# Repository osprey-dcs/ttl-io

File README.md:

# Osprey Quartz LVTTL I/O Daughter Board

A PMOD compatible board providing 4 input and 
4 output bits of LVTTL binary I/O.
Intended to be used with LBL [Marble](https://github.com/BerkeleyLab/Marble).

* [Current design](https://osprey-dcs.github.io/ttl-io) information.

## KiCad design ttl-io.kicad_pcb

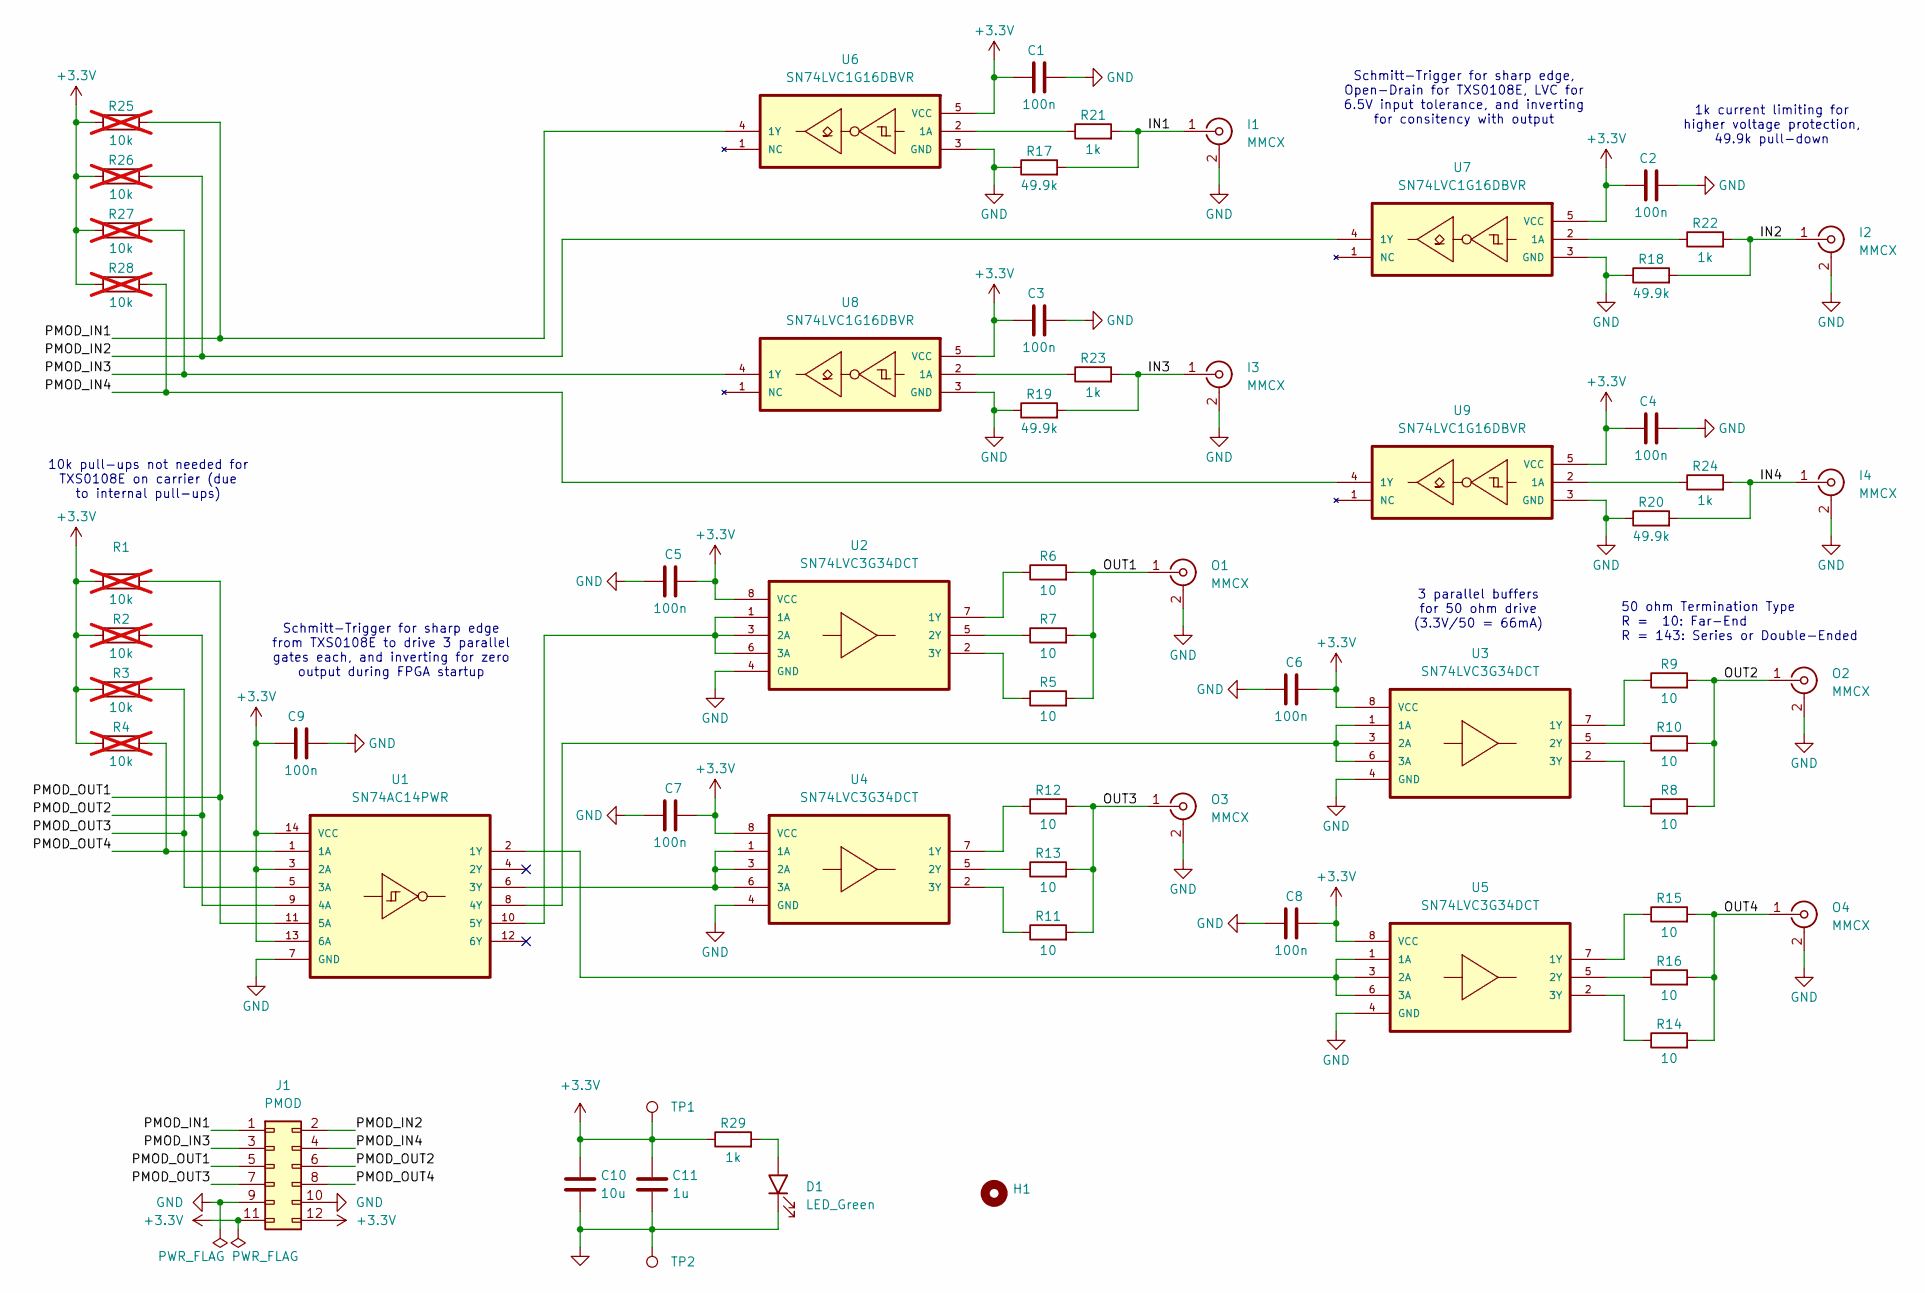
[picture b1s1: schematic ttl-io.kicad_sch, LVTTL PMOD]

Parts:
C1, C2, C3, C4, C5, C6, C7, C8, C9: 100n; C_0603_1608Metric; MPN CL10B104KB8NNWC; Digikey 1276-1935-2-ND
C10: 10u; C_0805_2012Metric; MPN GRM21BR61E106KA73L; Digikey 490-5523-2-ND
C11: 1u; C_0603_1608Metric; MPN CC0603KRX7R7BB105; Digikey 311-1446-2-ND
D1: LED_Green; LED_0603_1608Metric; MPN APT1608CGCK; Digikey 754-1116-2-ND
H1: Mounting_Hole_Slot
I1, I2, I3, I4: MMCX; MMCX_THT_Vertical; MPN MMCX-J-P-H-ST-TH1; Digikey SAM10617-ND
J1: PMOD; PMOD_2x06_P2.54mm_Mirrored; MPN PH2RA-12-UA; Digikey 2057-PH2RA-12-UA-ND
O1, O2, O3, O4: MMCX; MMCX_THT_Vertical; MPN MMCX-J-P-H-ST-TH1; Digikey SAM10617-ND
R1, R2, R3, R4, R25, R26, R27, R28: 10k; R_0603_1608Metric; MPN RC0603FR-0710KL; Digikey 311-10.0KHRCT-ND; not fitted
R5, R6, R7, R8, R9, R10, R11, R12, R13, R14, R15, R16: 10; R_0805_2012Metric; MPN RC0805FR-1010RL; Digikey 13-RC0805FR-1010RLTR-ND
R17, R18, R19, R20: 49.9k; R_0603_1608Metric; MPN RC0603FR-1349K9L; Digikey 13-RC0603FR-1349K9LTR-ND
R21, R22, R23, R24, R29: 1k; R_0603_1608Metric; MPN RC0603FR-071KP; Digikey YAG1294TR-ND
TP1: TestPointRed; TestPoint_Loop_D1.80mm_Drill1.0mm_Beaded; MPN 5000; Digikey 36-5000-ND
TP2: TestPointBlack; TestPoint_Loop_D1.80mm_Drill1.0mm_Beaded; MPN 5001; Digikey 36-5001-ND
U1: SN74AC14PWR; SN74AC1xPWR; MPN SN74AC14PWR; Digikey 296-4302-1-ND
U2, U3, U4, U5: SN74LVC3G34DCT; MPN SN74LVC3G34DCTR; Digikey 296-13285-1-ND
U6, U7, U8, U9: SN74LVC1G16DBVR; MPN SN74LVC1G16DBVR; Digikey 296-SN74LVC1G16DBVRCT-ND

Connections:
+3.3V: C1.2, C2.2, C3.2, C4.2, C5.2, C6.2, C7.2, C8.2, C9.2, C10.1, C11.1, J1.11, J1.12, R1.1, R2.1, R3.1, R4.1, R25.1, R26.1, R27.1, R28.1, R29.1, TP1.1, U1.3 (2A), U1.13 (6A), U1.14 (VCC), U2.8 (VCC), U3.8 (VCC), U4.8 (VCC), U5.8 (VCC), U6.5 (VCC), U7.5 (VCC), U8.5 (VCC), U9.5 (VCC)
/IN1: I1.1 (In), R17.2, R21.2
/IN2: I2.1 (In), R18.2, R22.2
/IN3: I3.1 (In), R19.2, R23.2
/IN4: I4.1 (In), R20.2, R24.2
/OUT1: O1.1 (In), R5.2, R6.2, R7.2
/OUT2: O2.1 (In), R8.2, R9.2, R10.2
/OUT3: O3.1 (In), R11.2, R12.2, R13.2
/OUT4: O4.1 (In), R14.2, R15.2, R16.2
/PMOD_IN1: J1.1, R25.2, U6.4 (1Y)
/PMOD_IN2: J1.2, R26.2, U7.4 (1Y)
/PMOD_IN3: J1.3, R27.2, U8.4 (1Y)
/PMOD_IN4: J1.4, R28.2, U9.4 (1Y)
/PMOD_OUT1: J1.5, R1.2, U1.11 (5A)
/PMOD_OUT2: J1.6, R2.2, U1.9 (4A)
/PMOD_OUT3: J1.7, R3.2, U1.5 (3A)
/PMOD_OUT4: J1.8, R4.2, U1.1 (1A)
GND: C1.1, C2.1, C3.1, C4.1, C5.1, C6.1, C7.1, C8.1, C9.1, C10.2, C11.2, D1.1 (K), I1.2 (Ext), I2.2 (Ext), I3.2 (Ext), I4.2 (Ext), J1.9, J1.10, O1.2 (Ext), O2.2 (Ext), O3.2 (Ext), O4.2 (Ext), R17.1, R18.1, R19.1, R20.1, TP2.1, U1.7 (GND), U2.4 (GND), U3.4 (GND), U4.4 (GND), U5.4 (GND), U6.3 (GND), U7.3 (GND), U8.3 (GND), U9.3 (GND)
unnamed: D1.2 (A), R29.2
unnamed: U1.2 (1Y), U5.1 (1A), U5.3 (2A), U5.6 (3A)
unnamed: U1.6 (3Y), U4.1 (1A), U4.3 (2A), U4.6 (3A)
unnamed: U1.8 (4Y), U3.1 (1A), U3.3 (2A), U3.6 (3A)
unnamed: U1.10 (5Y), U2.1 (1A), U2.3 (2A), U2.6 (3A)
unnamed: R6.1, U2.7 (1Y)
unnamed: R7.1, U2.5 (2Y)
unnamed: R5.1, U2.2 (3Y)
unnamed: R9.1, U3.7 (1Y)
unnamed: R10.1, U3.5 (2Y)
unnamed: R8.1, U3.2 (3Y)
unnamed: R12.1, U4.7 (1Y)
unnamed: R13.1, U4.5 (2Y)
unnamed: R11.1, U4.2 (3Y)
unnamed: R15.1, U5.7 (1Y)
unnamed: R16.1, U5.5 (2Y)
unnamed: R14.1, U5.2 (3Y)
unnamed: R21.1, U6.2 (1A)
unnamed: R22.1, U7.2 (1A)
unnamed: R23.1, U8.2 (1A)
unnamed: R24.1, U9.2 (1A)

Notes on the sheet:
Schmitt-Trigger for sharp edge from TXS0108E to drive 3 parallel gates each, and inverting for zero output during FPGA startup
Schmitt-Trigger for sharp edge, Open-Drain for TXS0108E, LVC for 6.5V input tolerance, and inverting for consitency with output
10k pull-ups not needed for TXS0108E on carrier (due to internal pull-ups)
3 parallel buffers for 50 ohm drive (3.3V/50 = 66mA)
50 ohm Termination Type R = 10: Far-End R = 143: Series or Double-Ended
1k current limiting for higher voltage protection, 49.9k pull-down

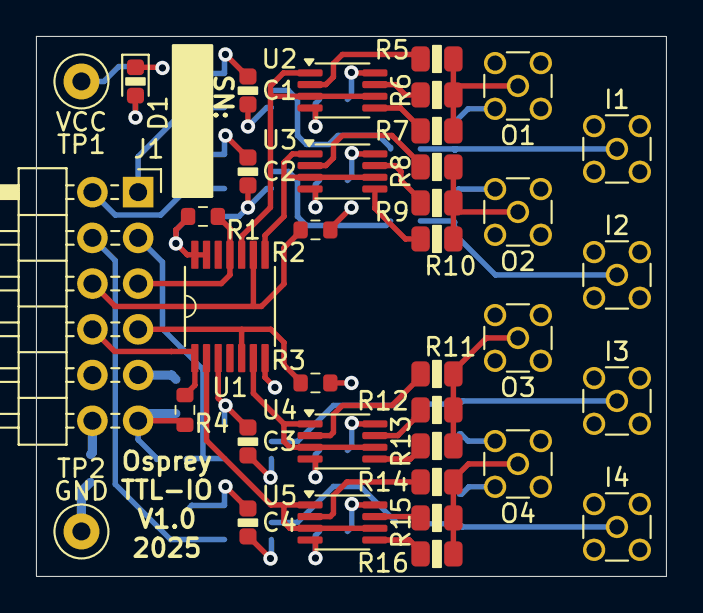
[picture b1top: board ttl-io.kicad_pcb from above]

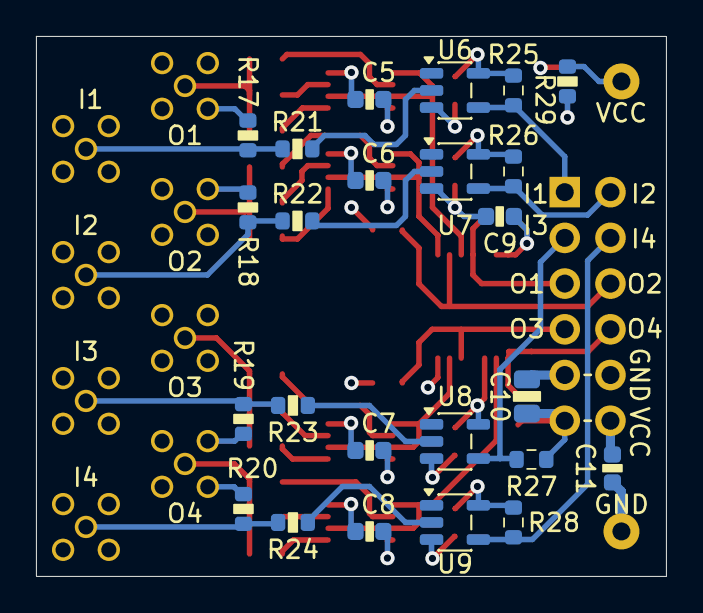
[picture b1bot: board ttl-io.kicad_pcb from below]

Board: 4 copper layers, 35.0 x 30.0 mm, 62 parts (24 on the bottom side), 39 nets.

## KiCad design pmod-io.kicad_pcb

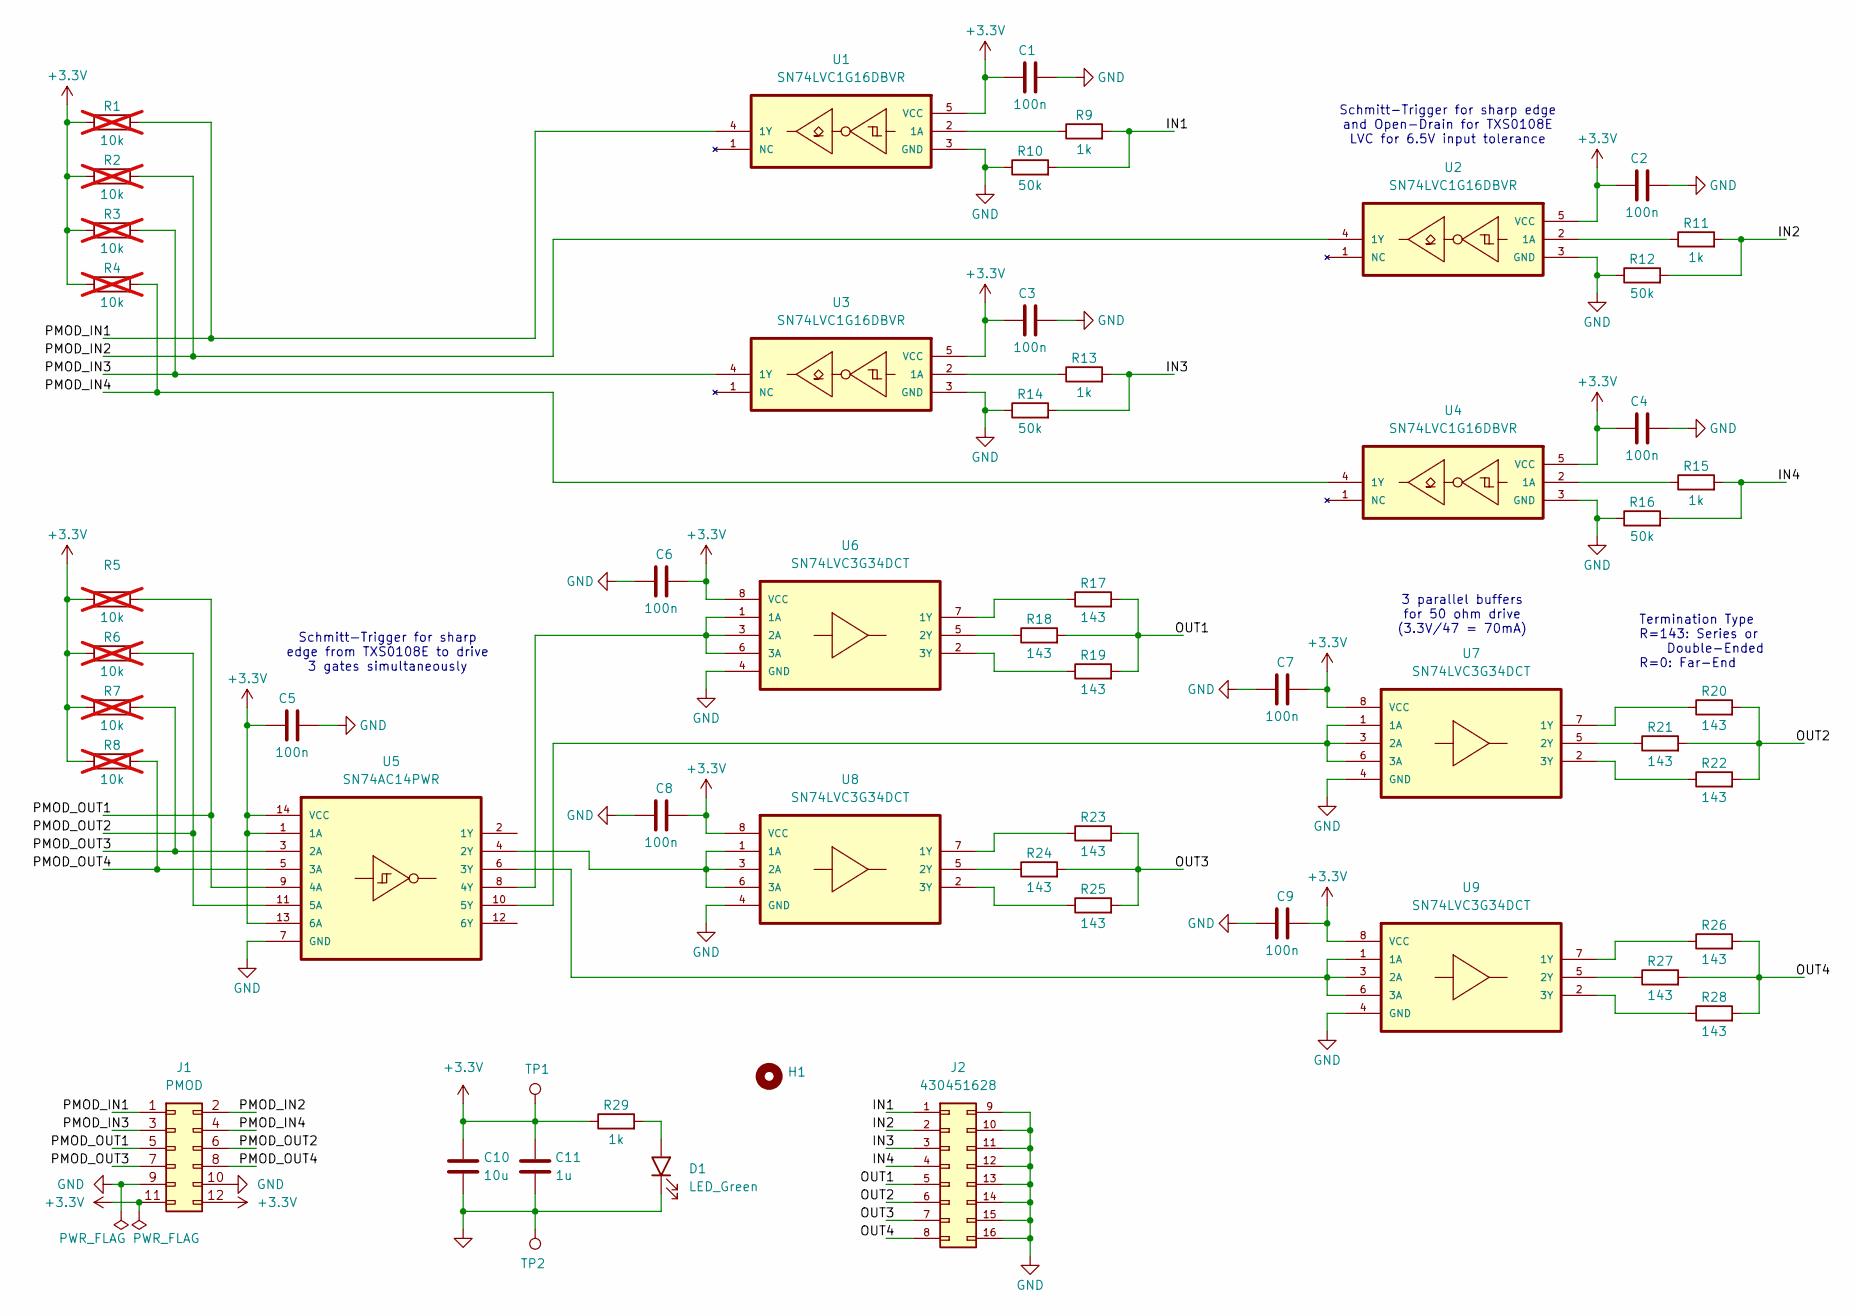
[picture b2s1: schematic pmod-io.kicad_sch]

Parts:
C1, C2, C3, C4, C5, C6, C7, C8, C9: 100n; C_0603_1608Metric; MPN CL10B104KB8NNWC; Digikey 1276-1935-2-ND
C10: 10u; C_0805_2012Metric; MPN GRM21BR61E106KA73L; Digikey 490-5523-2-ND
C11: 1u; C_0603_1608Metric; MPN CC0603KRX7R7BB105; Digikey 311-1446-2-ND
D1: LED_Green; LED_0603_1608Metric; MPN APT1608CGCK; Digikey 754-1116
H1: Mounting_Hole_Slot
J1: PMOD; PMOD_2x06_P2.54mm_Mirrored; MPN PH2RA-12-UA; Digikey 2057-PH2RA-12-UA-ND
J2: 430451628; MPN 0430451628; Digikey WM10719-ND
R1, R2, R3, R4, R5, R6, R7, R8: 10k; R_0603_1608Metric; MPN RC0603FR-0710KL; Digikey 311-10.0KHRCT-ND; not fitted
R9, R11, R13, R15: 1k; R_0603_1608Metric; MPN RC0603FR-0710KL; Digikey 311-10.0KHRCT-ND
R10, R12, R14, R16: 50k; R_0603_1608Metric; MPN RC0603FR-0710KL; Digikey 311-10.0KHRCT-ND
R17, R18, R19, R20, R21, R22, R23, R24, R25, R26, R27, R28: 143; R_0805_2012Metric; MPN RC0603FR-071KL; Digikey 311-1.00KCRTR-ND
R29: 1k; R_0603_1608Metric; MPN RC0603FR-071KL; Digikey 311-1.00KCRTR-ND
TP1: TestPoint; TestPoint_Loop_D1.80mm_Drill1.0mm_Beaded; MPN 5000; Digikey 36-5000-ND
TP2: TestPoint; TestPoint_Loop_D1.80mm_Drill1.0mm_Beaded; MPN 5001; Digikey 36-5001-ND
U1, U2, U3, U4: SN74LVC1G16DBVR; MPN SN74LVC1G16DBVR; Digikey 296-SN74LVC1G16DBVRCT-ND
U5: SN74AC14PWR; SN74AC1xPWR; MPN SN74AC14PWR; Digikey 296-4302-1-ND
U6, U7, U8, U9: SN74LVC3G34DCT; MPN SN74LVC3G34DCUR; Digikey 296-13285-1-ND

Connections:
+3.3V: C1.2, C2.2, C3.2, C4.2, C5.2, C6.2, C7.2, C8.2, C9.2, C10.1, C11.1, J1.11, J1.12, R1.1, R2.1, R3.1, R4.1, R5.1, R6.1, R7.1, R8.1, R29.1, TP1.1, U1.5 (VCC), U2.5 (VCC), U3.5 (VCC), U4.5 (VCC), U5.1 (1A), U5.13 (6A), U5.14 (VCC), U6.8 (VCC), U7.8 (VCC), U8.8 (VCC), U9.8 (VCC)
/IN1: J2.1, R9.2, R10.2
/IN2: J2.2, R11.2, R12.2
/IN3: J2.3, R13.2, R14.2
/IN4: J2.4, R15.2, R16.2
/OUT1: J2.5, R17.2, R18.2, R19.2
/OUT2: J2.6, R20.2, R21.2, R22.2
/OUT3: J2.7, R23.2, R24.2, R25.2
/OUT4: J2.8, R26.2, R27.2, R28.2
/PMOD_IN1: J1.1, R1.2, U1.4 (1Y)
/PMOD_IN2: J1.2, R2.2, U2.4 (1Y)
/PMOD_IN3: J1.3, R3.2, U3.4 (1Y)
/PMOD_IN4: J1.4, R4.2, U4.4 (1Y)
/PMOD_OUT1: J1.5, R5.2, U5.9 (4A)
/PMOD_OUT2: J1.6, R6.2, U5.11 (5A)
/PMOD_OUT3: J1.7, R7.2, U5.3 (2A)
/PMOD_OUT4: J1.8, R8.2, U5.5 (3A)
GND: C1.1, C2.1, C3.1, C4.1, C5.1, C6.1, C7.1, C8.1, C9.1, C10.2, C11.2, D1.1 (K), J1.9, J1.10, J2.9, J2.10, J2.11, J2.12, J2.13, J2.14, J2.15, J2.16, R10.1, R12.1, R14.1, R16.1, TP2.1, U1.3 (GND), U2.3 (GND), U3.3 (GND), U4.3 (GND), U5.7 (GND), U6.4 (GND), U7.4 (GND), U8.4 (GND), U9.4 (GND)
unnamed: D1.2 (A), R29.2
unnamed: R9.1, U1.2 (1A)
unnamed: R11.1, U2.2 (1A)
unnamed: R13.1, U3.2 (1A)
unnamed: R15.1, U4.2 (1A)
unnamed: U5.4 (2Y), U8.1 (1A), U8.3 (2A), U8.6 (3A)
unnamed: U5.6 (3Y), U9.1 (1A), U9.3 (2A), U9.6 (3A)
unnamed: U5.8 (4Y), U6.1 (1A), U6.3 (2A), U6.6 (3A)
unnamed: U5.10 (5Y), U7.1 (1A), U7.3 (2A), U7.6 (3A)
unnamed: R17.1, U6.7 (1Y)
unnamed: R18.1, U6.5 (2Y)
unnamed: R19.1, U6.2 (3Y)
unnamed: R20.1, U7.7 (1Y)
unnamed: R21.1, U7.5 (2Y)
unnamed: R22.1, U7.2 (3Y)
unnamed: R23.1, U8.7 (1Y)
unnamed: R24.1, U8.5 (2Y)
unnamed: R25.1, U8.2 (3Y)
unnamed: R26.1, U9.7 (1Y)
unnamed: R27.1, U9.5 (2Y)
unnamed: R28.1, U9.2 (3Y)

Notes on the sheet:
Schmitt-Trigger for sharp edge from TXS0108E to drive 3 gates simultaneously
Schmitt-Trigger for sharp edge and Open-Drain for TXS0108E LVC for 6.5V input tolerance
3 parallel buffers for 50 ohm drive (3.3V/47 = 70mA)
Termination Type R=143: Series or Double-Ended R=0: Far-End

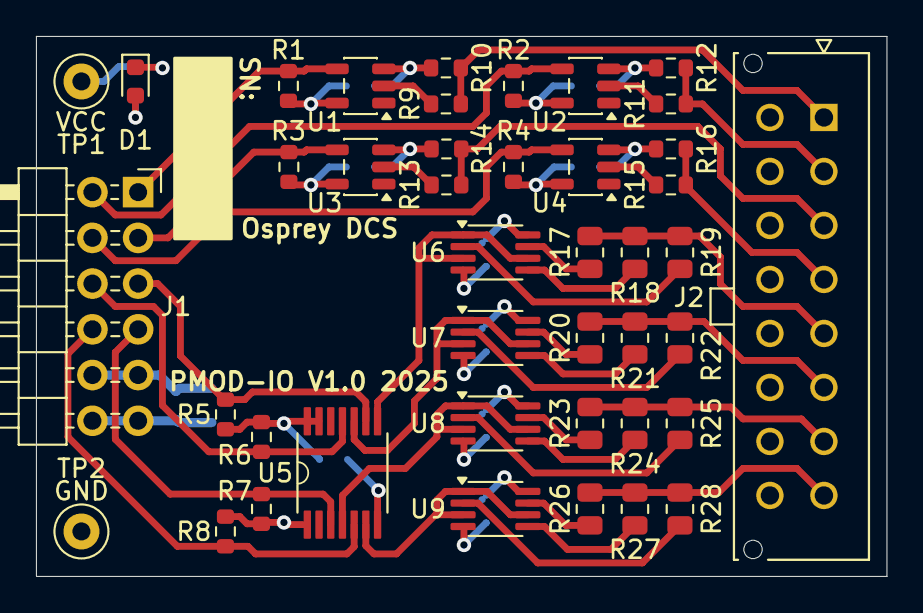
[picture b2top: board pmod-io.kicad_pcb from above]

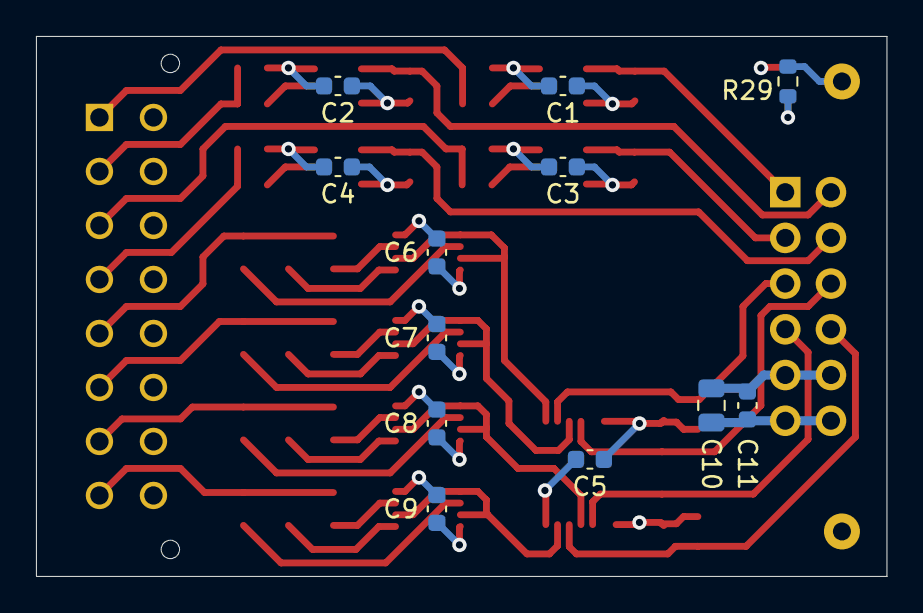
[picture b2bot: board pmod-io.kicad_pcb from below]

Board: 4 copper layers, 47.2 x 30.0 mm, 55 parts (12 on the bottom side), 39 nets.

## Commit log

2025-10-22 Passed DRC, ready to build?
2025-10-23 Ready for review
2025-10-25 Updated part values/#s
2025-10-28 Updated sch notes and part info, ready for fab
2025-10-29 gitattributes
2025-10-29 apply gitignore
2025-10-29 switch to unix eol
2025-10-29 add GHA
2025-10-29 add title and copyright/license
    adjust PCB page size to US letter
2025-10-29 set silk/paste colors
2025-10-29 add 3d model for I/O connector
2025-10-29 add gh-pages
2025-10-29 fix gh-pages
2025-10-29 add wire harness sub-project
2025-10-29 pcb tweaks, date/ver, U5 3D model, 0.4mm holes
2025-10-29 update io-cable
2025-10-29 drop fp-info-cache
2025-11-04 30x35mm version initial commit
2025-11-04 initial 30mm x 35mm STEP file
2025-11-05 swapped I/O MMCX columns
2025-11-11 slotted mounting hole
2025-11-12 Updated 0805 resistor part #
2025-11-12 Fixed 10 ohm res part #
2025-11-15 switch EoL to CRLF
2025-11-15 set ENIG finish
2025-11-15 kibot: model include silk
2025-11-15 add silkscreen bar under passives which should be placed
2025-11-15 fixup! kibot: model include silk
2025-11-15 kibot: export 3d model for rendering
2025-11-15 drop out of date io-cable
2025-11-15 add render to README
2025-12-21 add photograph
2026-01-07 add COPYRIGHT

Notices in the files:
ttl-io.kicad_pcb:
SPDX-FileCopyrightText: 2025 Osprey DCS
SPDX-License-Identifier: CERN-OHL-S-2.0+
